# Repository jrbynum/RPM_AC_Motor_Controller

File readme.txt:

RPM AC Motor Controller

This is an Arduino based motor controller that uses a reflective optical sensor to calculate rpm and an LM135
to compute temperature. It uses the PID library to compute feedback. RPM and Temperature are displayed on an LCD. 

A zero crossing circuit and triac are used to control the set RPM which is based upon a 10K pot. The circuit 
can also be controlled using a pwm input. This input could be used from Mach3.

11/02/2013 - Added an Eagle Schematic and Board layout for an Arduino shield that will be used for development.

Rusty Bynum
jrbynum@shaw.ca

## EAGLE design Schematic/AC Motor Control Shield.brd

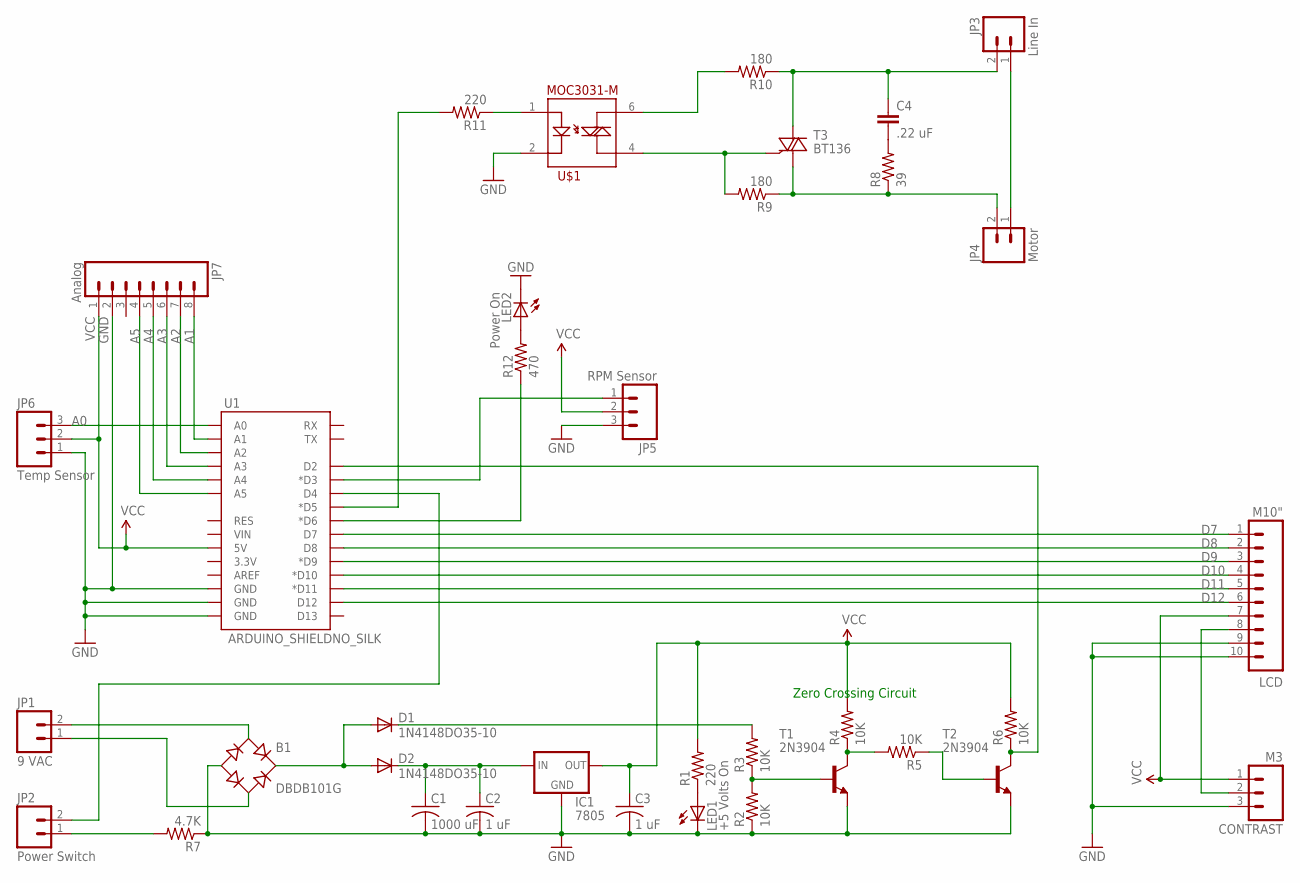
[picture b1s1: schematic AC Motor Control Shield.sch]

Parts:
B1: DBDB101G; DB
C1: 1000 uF; C050-035X075
C2, C3: 1 uF; C050-035X075
C4: .22 uF; CAP-PTH-LARGE
CONTRAST: M3; 1X03
D1, D2: 1N4148DO35-10; DO35-10
IC1: 7805; TO-220-ALT
JP1: 9 VAC; SCREWTERMINAL-5MM-2
JP2: Power Switch; 1X02
JP3: Line In; SCREWTERMINAL-5MM-2
JP4: Motor; SCREWTERMINAL-5MM-2
JP5: RPM Sensor; 1X03
JP6: Temp Sensor; 1X03
JP7: Analog; 1X08
LCD: M10"; 1X10
LED1: +5 Volts On; LED5MM
LED2: Power On; LED5MM
R1, R11: 220; 0207/10
R2, R3, R4, R5, R6: 10K; 0207/10
R7: 4.7K; 0207/10
R8: 39; AXIAL-0.6
R9, R10: 180; AXIAL-0.6
R12: 470; 0207/10
T1, T2: 2N3904; TO92
T3: BT136; TO220AB
U1: ARDUINO_SHIELDNO_SILK; DUEMILANOVE_VIAS
U$1: MOC3031-M; DIL06

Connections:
A0: JP6.3, U1.A0
A1: JP7.8, U1.A1
A2: JP7.7, U1.A2
A3: JP7.6, U1.A3
A4: JP7.5, U1.A4
A5: JP7.4, U1.A5
D7: LCD.1, U1.D7
D8: LCD.2, U1.D8
D9: LCD.3, U1.D9 (*D9)
D10: LCD.4, U1.D10 (*D10)
D11: LCD.5, U1.D11 (*D11)
D12: LCD.6, U1.D12
GND: B1.-, C1.2, C2.2, C3.2, CONTRAST.3, IC1.GND, JP5.3, JP6.1, JP7.2, LCD.9, LCD.10, LED1.K (C), LED2.K (C), R2.1, R7.1, T1.3 (E), T2.3 (E), U1.GND@0 (GND), U1.GND@1 (GND), U1.GND@2 (GND), U$1.2
unnamed: B1.AC2, JP1.1
unnamed: B1.AC1, JP1.2
unnamed: R5.1, T2.2 (B)
unnamed: B1.+, D1.A, D2.A
unnamed: D1.C, R3.2
unnamed: C1.1, C2.1, D2.C, IC1.IN
unnamed: JP2.1, R7.2
unnamed: LED1.A, R1.1
unnamed: R2.2, R3.1, T1.2 (B)
unnamed: R4.1, R5.2, T1.1 (C)
unnamed: R6.1, T2.1 (C), U1.D2
unnamed: JP2.2, U1.D4
unnamed: JP3.1, JP4.1
unnamed: C4.2, R8.P$2 (2)
unnamed: C4.1, JP3.2, R10.P$1 (1), T3.2 (A2)
unnamed: JP4.2, R8.P$1 (1), R9.P$1 (1), T3.1 (A1)
unnamed: R9.P$2 (2), T3.3 (G), U$1.4
unnamed: R10.P$2 (2), U$1.6
unnamed: R11.1, U$1.1
unnamed: R11.2, U1.D5 (*D5)
unnamed: JP5.1, U1.D3 (*D3)
unnamed: CONTRAST.2, LCD.8
unnamed: LED2.A, R12.2
unnamed: R12.1, U1.D6 (*D6)
VCC: C3.1, CONTRAST.1, IC1.OUT, JP5.2, JP6.2, JP7.1, LCD.7, R1.2, R4.2, R6.2, U1.5V

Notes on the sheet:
Zero Crossing Circuit

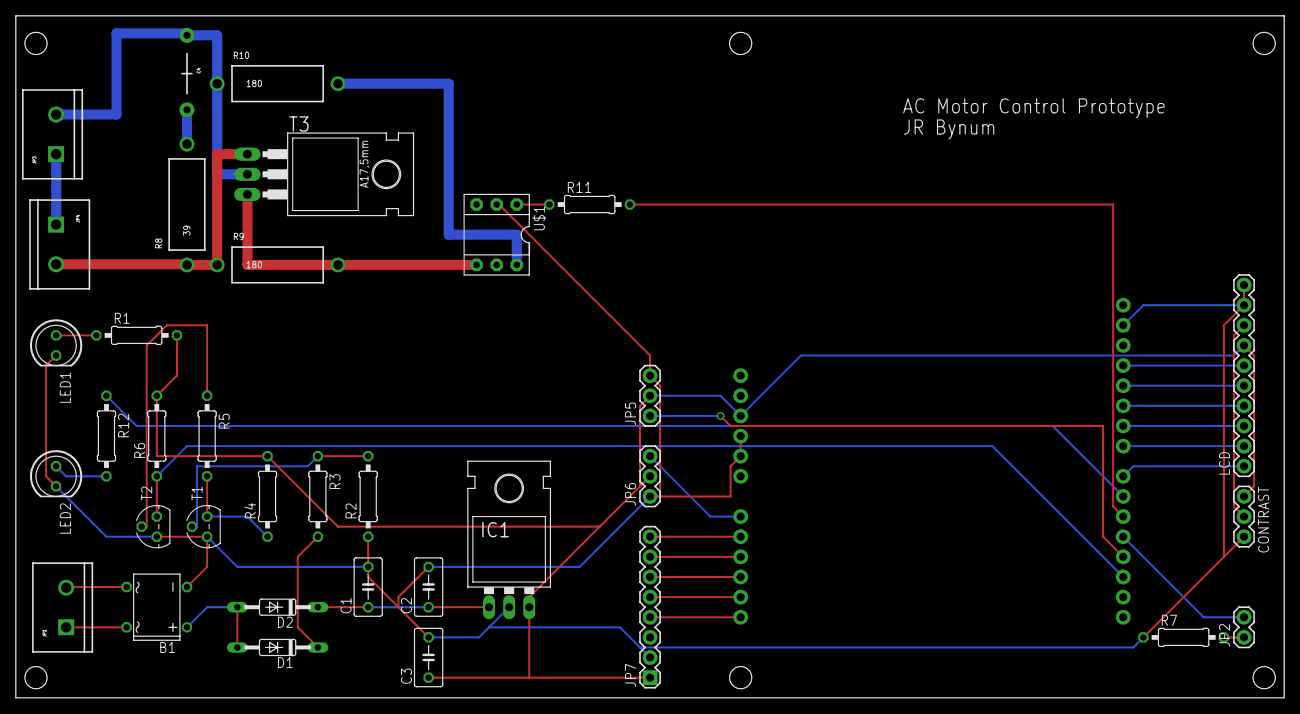
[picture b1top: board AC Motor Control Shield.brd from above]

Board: 2 copper layers, 160.0 x 86.0 mm, 36 parts (0 on the bottom side), 38 nets.

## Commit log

2013-02-11 Initial Create
    Basic Code - setup to use MariaMole IDE for the Arduino.
    TCRT5000 Reflective Optical Sensor implemented
    LM135 Tempertaure Sensor implemented
    Lots left todo!
2013-02-11 Added Readme file
2013-02-12 Intial prototype schematic for development
2013-02-12 Updated Readme File

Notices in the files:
parts and their libraries:
SparkFun-Boards: Licensing: CC v3.0 Share-Alike You are welcome to use this library for commercial purposes.
